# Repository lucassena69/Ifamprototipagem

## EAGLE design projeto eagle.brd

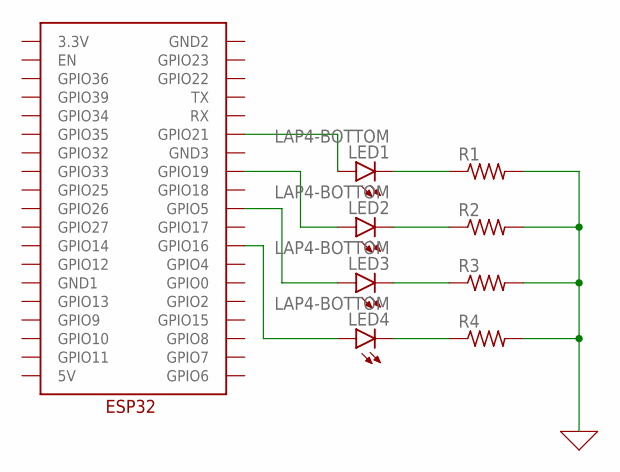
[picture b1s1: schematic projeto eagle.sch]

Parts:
LED1, LED2, LED3, LED4: LAP4-BOTTOM; P47F-BOTTOM
R1, R2, R3, R4: R-US_0204/2V; 0204V
U$1: ESP32

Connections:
0: R1.2, R2.2, R3.2, R4.2
unnamed: LED1.C, R1.1
unnamed: LED2.C, R2.1
unnamed: LED3.C, R3.1
unnamed: LED4.C, R4.1
unnamed: LED1.A, U$1.GPIO21
unnamed: LED2.A, U$1.GPIO19
unnamed: LED3.A, U$1.GPIO5
unnamed: LED4.A, U$1.GPIO16

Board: 2 copper layers, 9 parts (0 on the bottom side), 9 nets, no tracks yet.
